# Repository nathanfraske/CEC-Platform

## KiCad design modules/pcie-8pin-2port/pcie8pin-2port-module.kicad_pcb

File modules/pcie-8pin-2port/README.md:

# PCIe 8-pin module — 2-port SKU

Standard-tier **per-cable** sensing module for the PCIe 8-pin (PCIe/GPU) power
connector. **2-port SKU: 2 cables → 4 connectors**. The 3-port variant (spec
upper bound) is a separate board in
[`../pcie-8pin-3port`](../pcie-8pin-3port). BOM target **$38** (100-qty). See spec
[§6.2](../../CEC-Platform-Ground-Truth-Spec.md).

| Item | Decision |
|---|---|
| Tier | Standard |
| SKU | **2-port** (2 cables / 4 connectors) — SKU separation from the 3-port |
| MCU | **ESP32-C6-MINI-1-N4** (v3.10; was ESP32-S3-MINI-1-N4R2). Native USB-Serial-JTAG on IO13 (D+)/IO12 (D−); ADC1 = GPIO0–6. |
| Hub link | RJ-45 8P8C shielded FTP, locking boot (J1) |
| Power path | Pass-through interposer: per cable a PSU-side **IN** + load-side **OUT** 8-pin (2×4) header; **2 cables → 4 headers**. Molex Mini-Fit Jr (PCIe/ATX 8-pin standard; 3×12V + 5×GND). Gender/footprint per the 24-pin §2.8 interposer pattern — confirm at layout. |
| Control | CAN on pair 3 (classical 500 kbps in a Standard Hub), TJA1051T/3 (U2) |
| Sensing | **Per-cable INA238** (16-bit I²C), 2 cables (U10/U11, distinct I²C addresses) — one across each cable's **0.5 mΩ** Kelvin shunt (RS1/RS2, §6.4), Vbus read on the load side. |
| Transient detection (§6.13) | **Per-cable analog DETECTION front-end** (v3.10, resolves OQ-9): INA181A2 gain-50 CSA (U20/U21) → TLV7011 hysteresis comparator (U30/U31) → board-shared firmware THRESH (MCU PWM IO14 + R10 10 kΩ / C40 100 nF) → per-cable DET → MCU GPIO, ORs into the §6.10 FREEZE trigger. Binary event (it happened + averaged envelope), not the sub-ms waveform — magnitude/shape are a PCIe Pro/Max SKU. |
| Streaming | RS-485 **not populated** (Standard); pair 2 terminated module-side |
| DETECT | 2.2 kΩ precision (R1) — CAN-only code (§2.3, OQ-6 resolved), Hub 10 kΩ/3.3 V divider; poke-and-ack tap R7 → IO10 (OQ-28) |
| Protection | No per-pin PoE/over-voltage (Standard/Pro, §2.4 v2.0); low-cap ESD diode D1 (**PESD5V0S1BA**, C5261083) on DETECT pin 8 |
| Flash/debug | USB-C (J5) on the ESP32-C6 native USB-Serial-JTAG (D+ = IO13 / D− = IO12) + BOOT/RESET buttons (SW1/SW2, TS-1088-AR02016; BOOT = IO9); VBUS ORs into +5VSB via D2 (SS34); CC1/CC2 = 5.1 kΩ |
| Decoupling | LP5907 LDO; 24-pin gold-standard tiering (2× 10 µF bulk, 1 µF LDO in/out, per-IC 100 nF) |
| BOM target | $38 (100-qty) |

## Open questions touching this board

- **OQ-9 (RESOLVED, v3.10 §6.13):** PCIe transient capture is the analog DETECTION
  ladder above — Standard sees that a transient happened (binary, into FREEZE);
  magnitude/shape are held to the PCIe Pro/Max SKUs. (OQ-57..59 gate the details.)
- **OQ-10 / OQ-12:** bundled-shunt vertical transition + high-current stackup for
  the ~40–55 A/cable shunt sites (§6.7).
- **OQ-11:** per-module shunt part selection (§6.4 table).
- *(OQ-6 module-ID encoding resolved — CAN-only modules = 2.2 kΩ.)*

## Status

Schematic generated by `scripts/gen-modules.py`; the initial PCB floorplan by
`scripts/gen-module-pcb.py` (one-shot — hand-maintained in the GUI afterwards):
4-layer, **2 oz outer / 1 oz inner** (In1 = GND, In2 = 12 V), ~110 × 66 mm, 2
cables inline top/bottom, the ESP + CAN + LDO + flash front end + RJ-45 on the
right, 4× M3 corner mounts (cables inset to clear them), CEC copper logo on the
back. **DRAFT** marker present (ERC/DRC not yet CI-gated). Next in GUI: *Update
PCB from Schematic* to pull the passives, then place/route + pour (§6.8 Kelvin
taps, §6.7 high-current transitions). Project-local library tables point at
`../../lib` via `${KIPRJMOD}`.

## Update (2026-06-06) — v3.10: ESP32-C6 MCU + §6.13 transient-detection front-end

Regenerated on the consolidated v3.10 spec:

- **MCU ESP32-S3-MINI-1-N4R2 → ESP32-C6-MINI-1-N4** (C5736265), pin map
  netlist-verified (CAN_TX/RX → pads 26/27, USB D+/D− → pads 18/17, I²C → 24/25,
  EN → 8, BOOT/IO9 → 23, DETECT_SENSE → 12, +3V3 → 3, THRESH_PWM/IO14 → 19).
  Footprint `cec-RF_Module:ESP32-C6-MINI-1`.
- **§6.13 per-cable detection front-end** (2 cables): U20/U21 **INA181A2IDBVR**
  (C2058784) + U30/U31 **TLV7011DBVR** (C702117) + board-shared R10/C40 THRESH RC
  off MCU PWM IO14. Chain netlist-verified (shunt → INA181 → comparator → THRESH →
  per-cable DET → MCU GPIO pads 28/29). **D1 PESD UL → BA** (C5261083).
- BOM regenerated (`bom/pcie8pin-2port-module-BOM-jlcpcb.csv`): **sourced 39/45**;
  open are the 0.5 mΩ shunts (OQ-11) + the Mini-Fit Jr THT power headers.
- ERC = benign only.

## PCB floorplan (2026-06-06) — condensed candidate generator (86.4 × 44 mm)

Reproduced by `scripts/gen-pcie-condensed.py` (the **parametric** PCIe analogue of the
EPS `gen-eps-condensed.py`; reuses `gen-module-pcb.py`'s emit helpers without touching the
shared generator — one script drives both PCIe SKUs by board-name arg). Built the EPS way,
with **two sub-agent passes — footprint/placement planning, then a routing game-plan**.
**86.4 × 44 mm** (4-layer, F.Cu 2 oz / In1 1 oz / In2 1 oz / B.Cu 2 oz) — condensed from the
earlier 99 × 44. Plan + diagram: `pcie2-routing-plan.png`. **All 45 schematic parts placed**
(25/25 support passives netlist-verified by `PASSIVE_SPEC` + explicitly cluster-placed — the
3 entries for the 3rd cable are correctly absent on this 2-cable SKU); DRC 0 structural apart
from a known headless false within-footprint mask-bridge artifact on a button (absent in the
GUI; the RJ-45 mouth overhangs with copper kept on-board).

- **Cable connectors = the REAL Molex 45586** (J_IN/J_OUT): **Mini-Fit Jr. right-angle,
  3rd-gen PCIe polarization, 8-circuit, Nylon UL94V-0, 2.54µm matte tin — MPN
  45586-0005** (user-confirmed keying). The footprint is the manufacturer ECAD land
  (`cec-Connector_Molex:Molex_Mini-Fit_Jr_45586_2x04_P4.20mm_Horizontal`, vendored from
  the Molex `-SD` export + its STEP): 4.20 mm pitch + **5.50 mm rows**, round ⌀2.36 mm /
  1.85 mm-drill pads, two ⌀3.0 mm snap pegs in line with the outer pins 7.3 mm forward.
  THT, consigned/hand-soldered.
- **Connectors overhang their edges** — the body+mouth hang off the top (J_IN) /
  bottom (J_OUT) edges; only the pad rows + the 2 snap pegs stay on-board. The
  footprint is native mouth-toward-+y, so J_IN is placed rot180 / J_OUT rot0 (which
  reproduces the prior pad columns, so the net map + 12 V alignment are unchanged).
  The **RJ-45 mouth overhangs the right edge** too. The 45586 snap pegs set H = 44.
- **Side-by-side sense band** per cable: 0.5 mΩ shunt vertical in the 12 V path, INA238 +
  the §6.13 INA181→TLV7011 pair beside it.
- **J1 = platform FTP jack** Kinghelm **KH-RJ45-58-8P8C** (LCSC **C2683360**,
  `cec:RJ45_FTP_Shielded_Horizontal`), SH1/SH2 → GND — matching the Hub, EPS and
  12VHPWR.
- **3 M3 mounts:** two on the logic/electronics (right) side (TR/BR corners) + **one
  centered on the connector (left) side** at (4, H/2). USB-C on the top edge.
- Dual `GND Plane` over In1 + In2 (12 V on the outers, split at the shunt), emitted
  unfilled. Routing-candidate guides on user layers (12 V pours Dwgs.User, Kelvin pairs
  Cmts.User, control→sense spine Eco1.User, CAN/USB Eco2.User). CEC logo + fab note on back.

**Next in the GUI:** *Fill All Zones*, route (§6.8 Kelvin taps, §6.7 high-current
transitions), re-DRC. Regenerate (pre-route only) with
`python3 scripts/gen-pcie-condensed.py pcie-8pin-2port` — one-shot bootstrap, refuses to
overwrite once tracks/vias exist (`--force` overrides); hand-maintained from the first route.

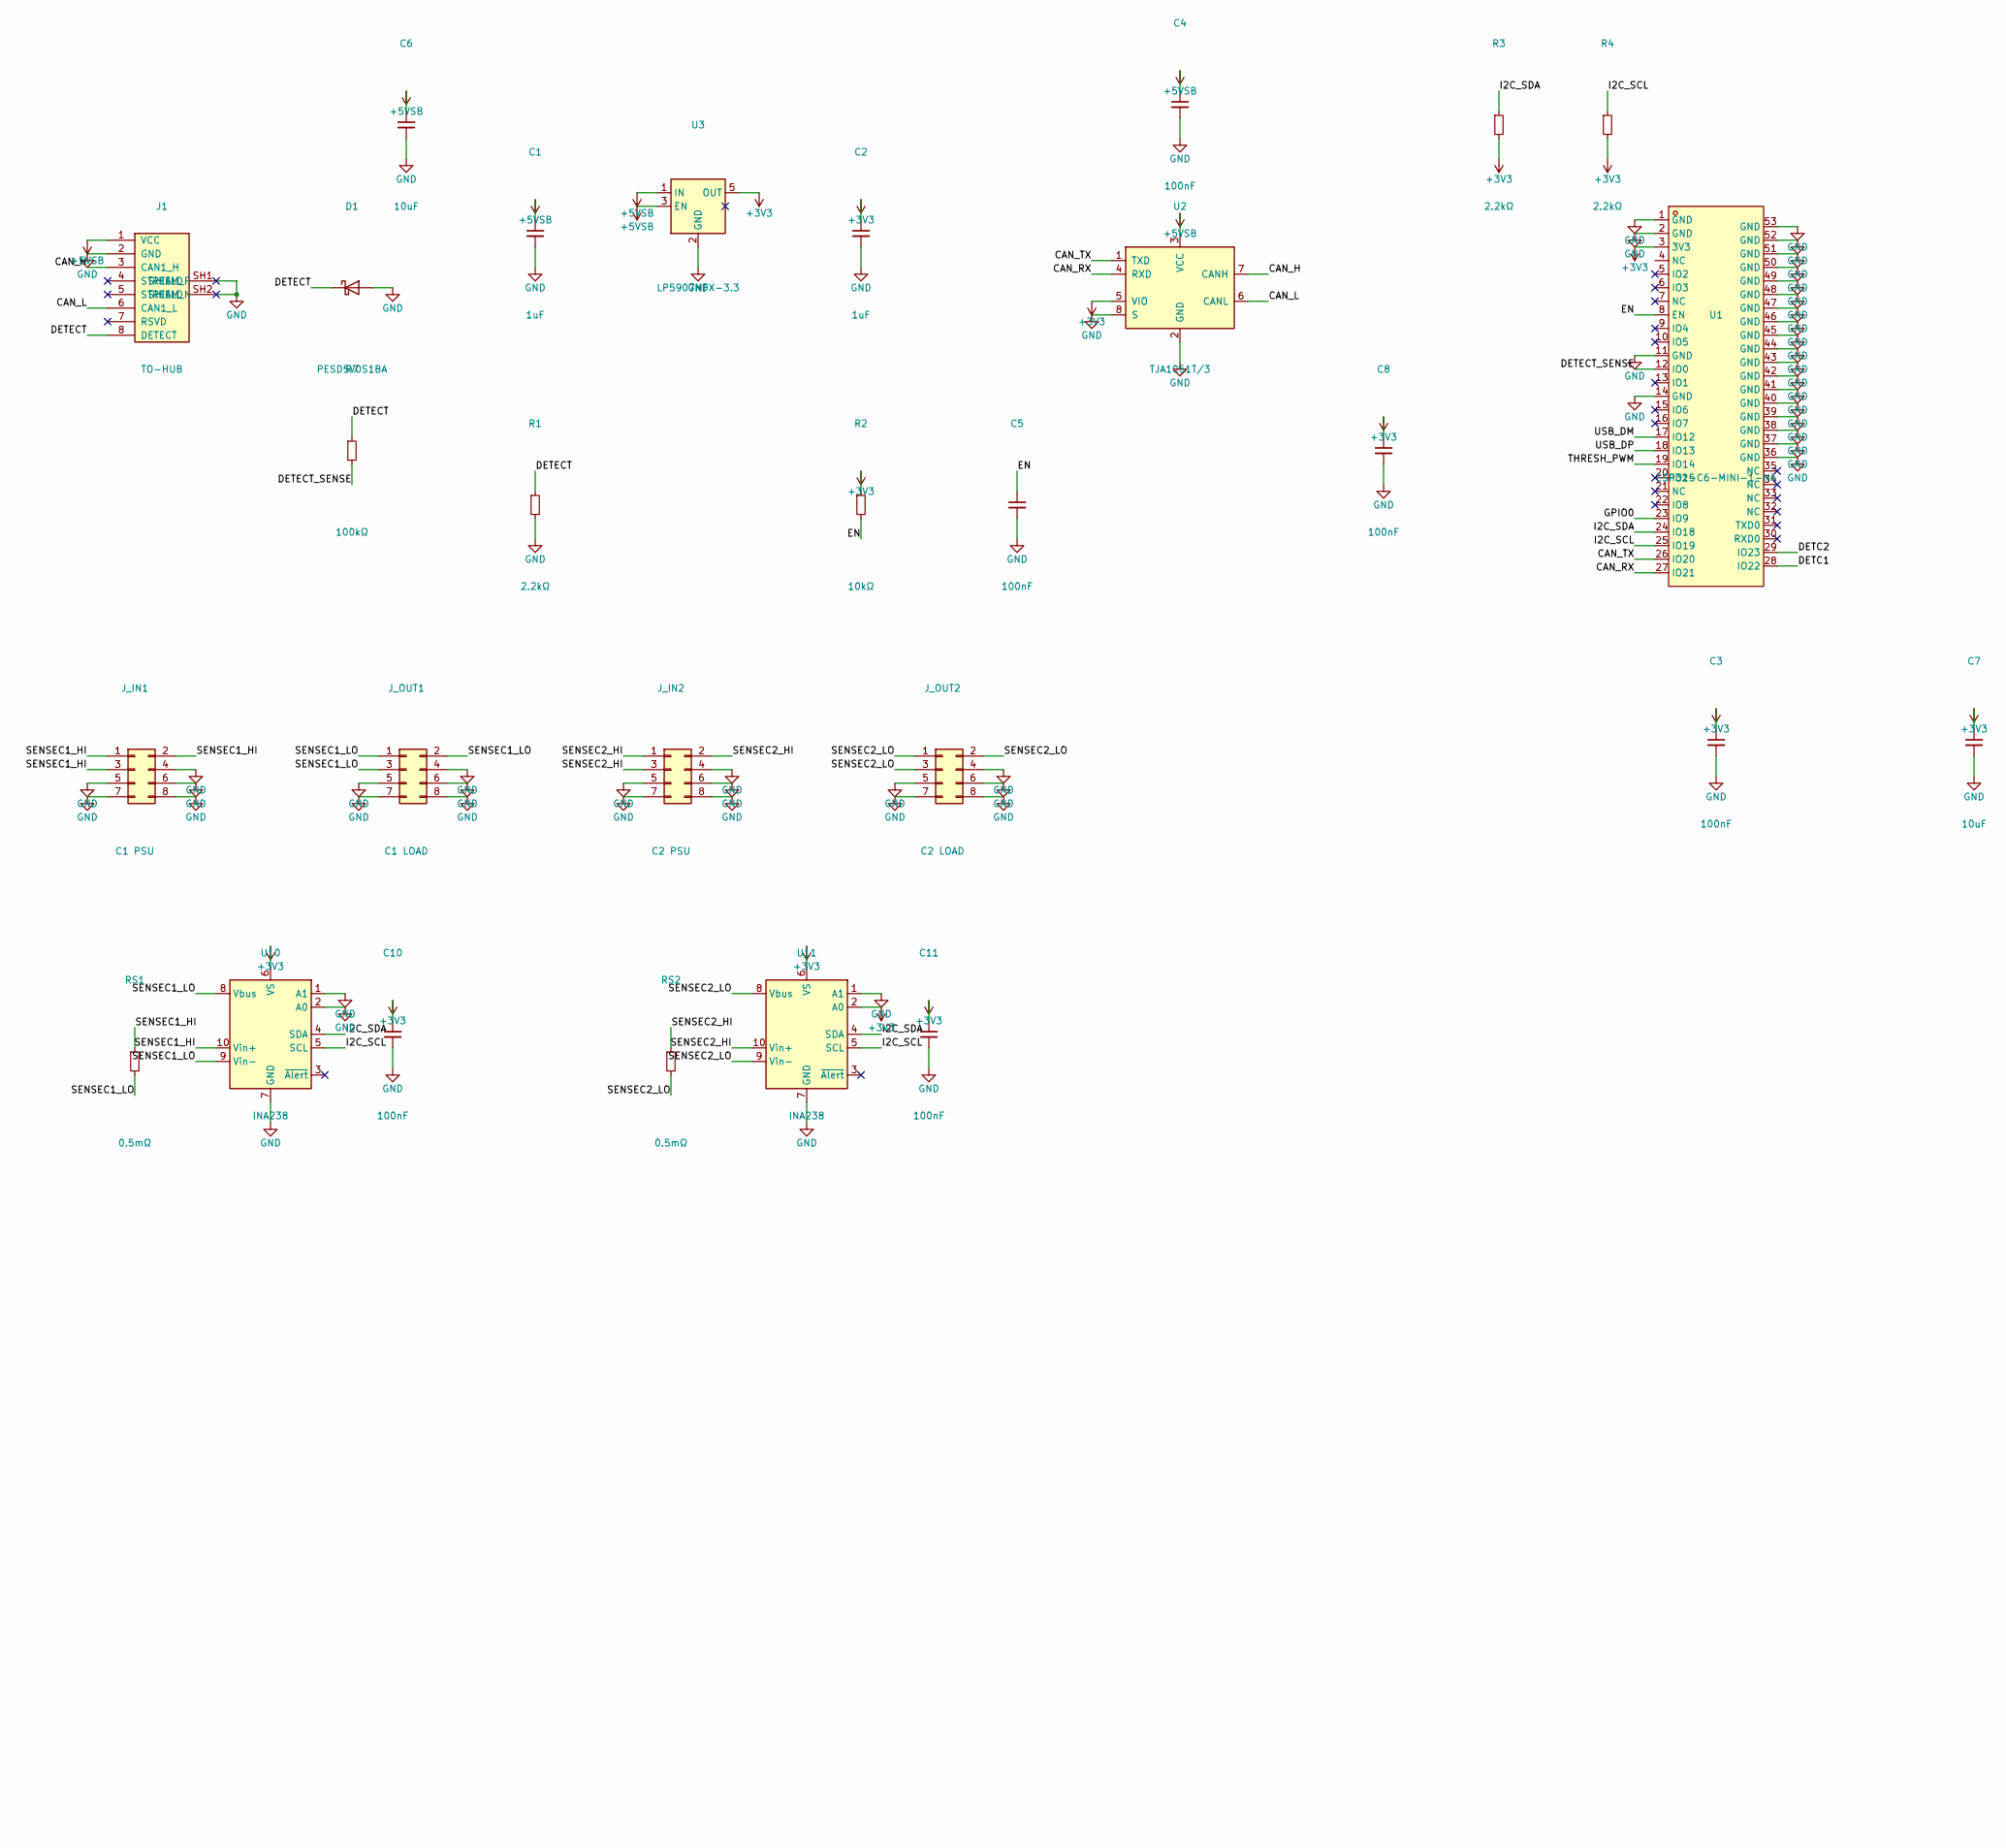
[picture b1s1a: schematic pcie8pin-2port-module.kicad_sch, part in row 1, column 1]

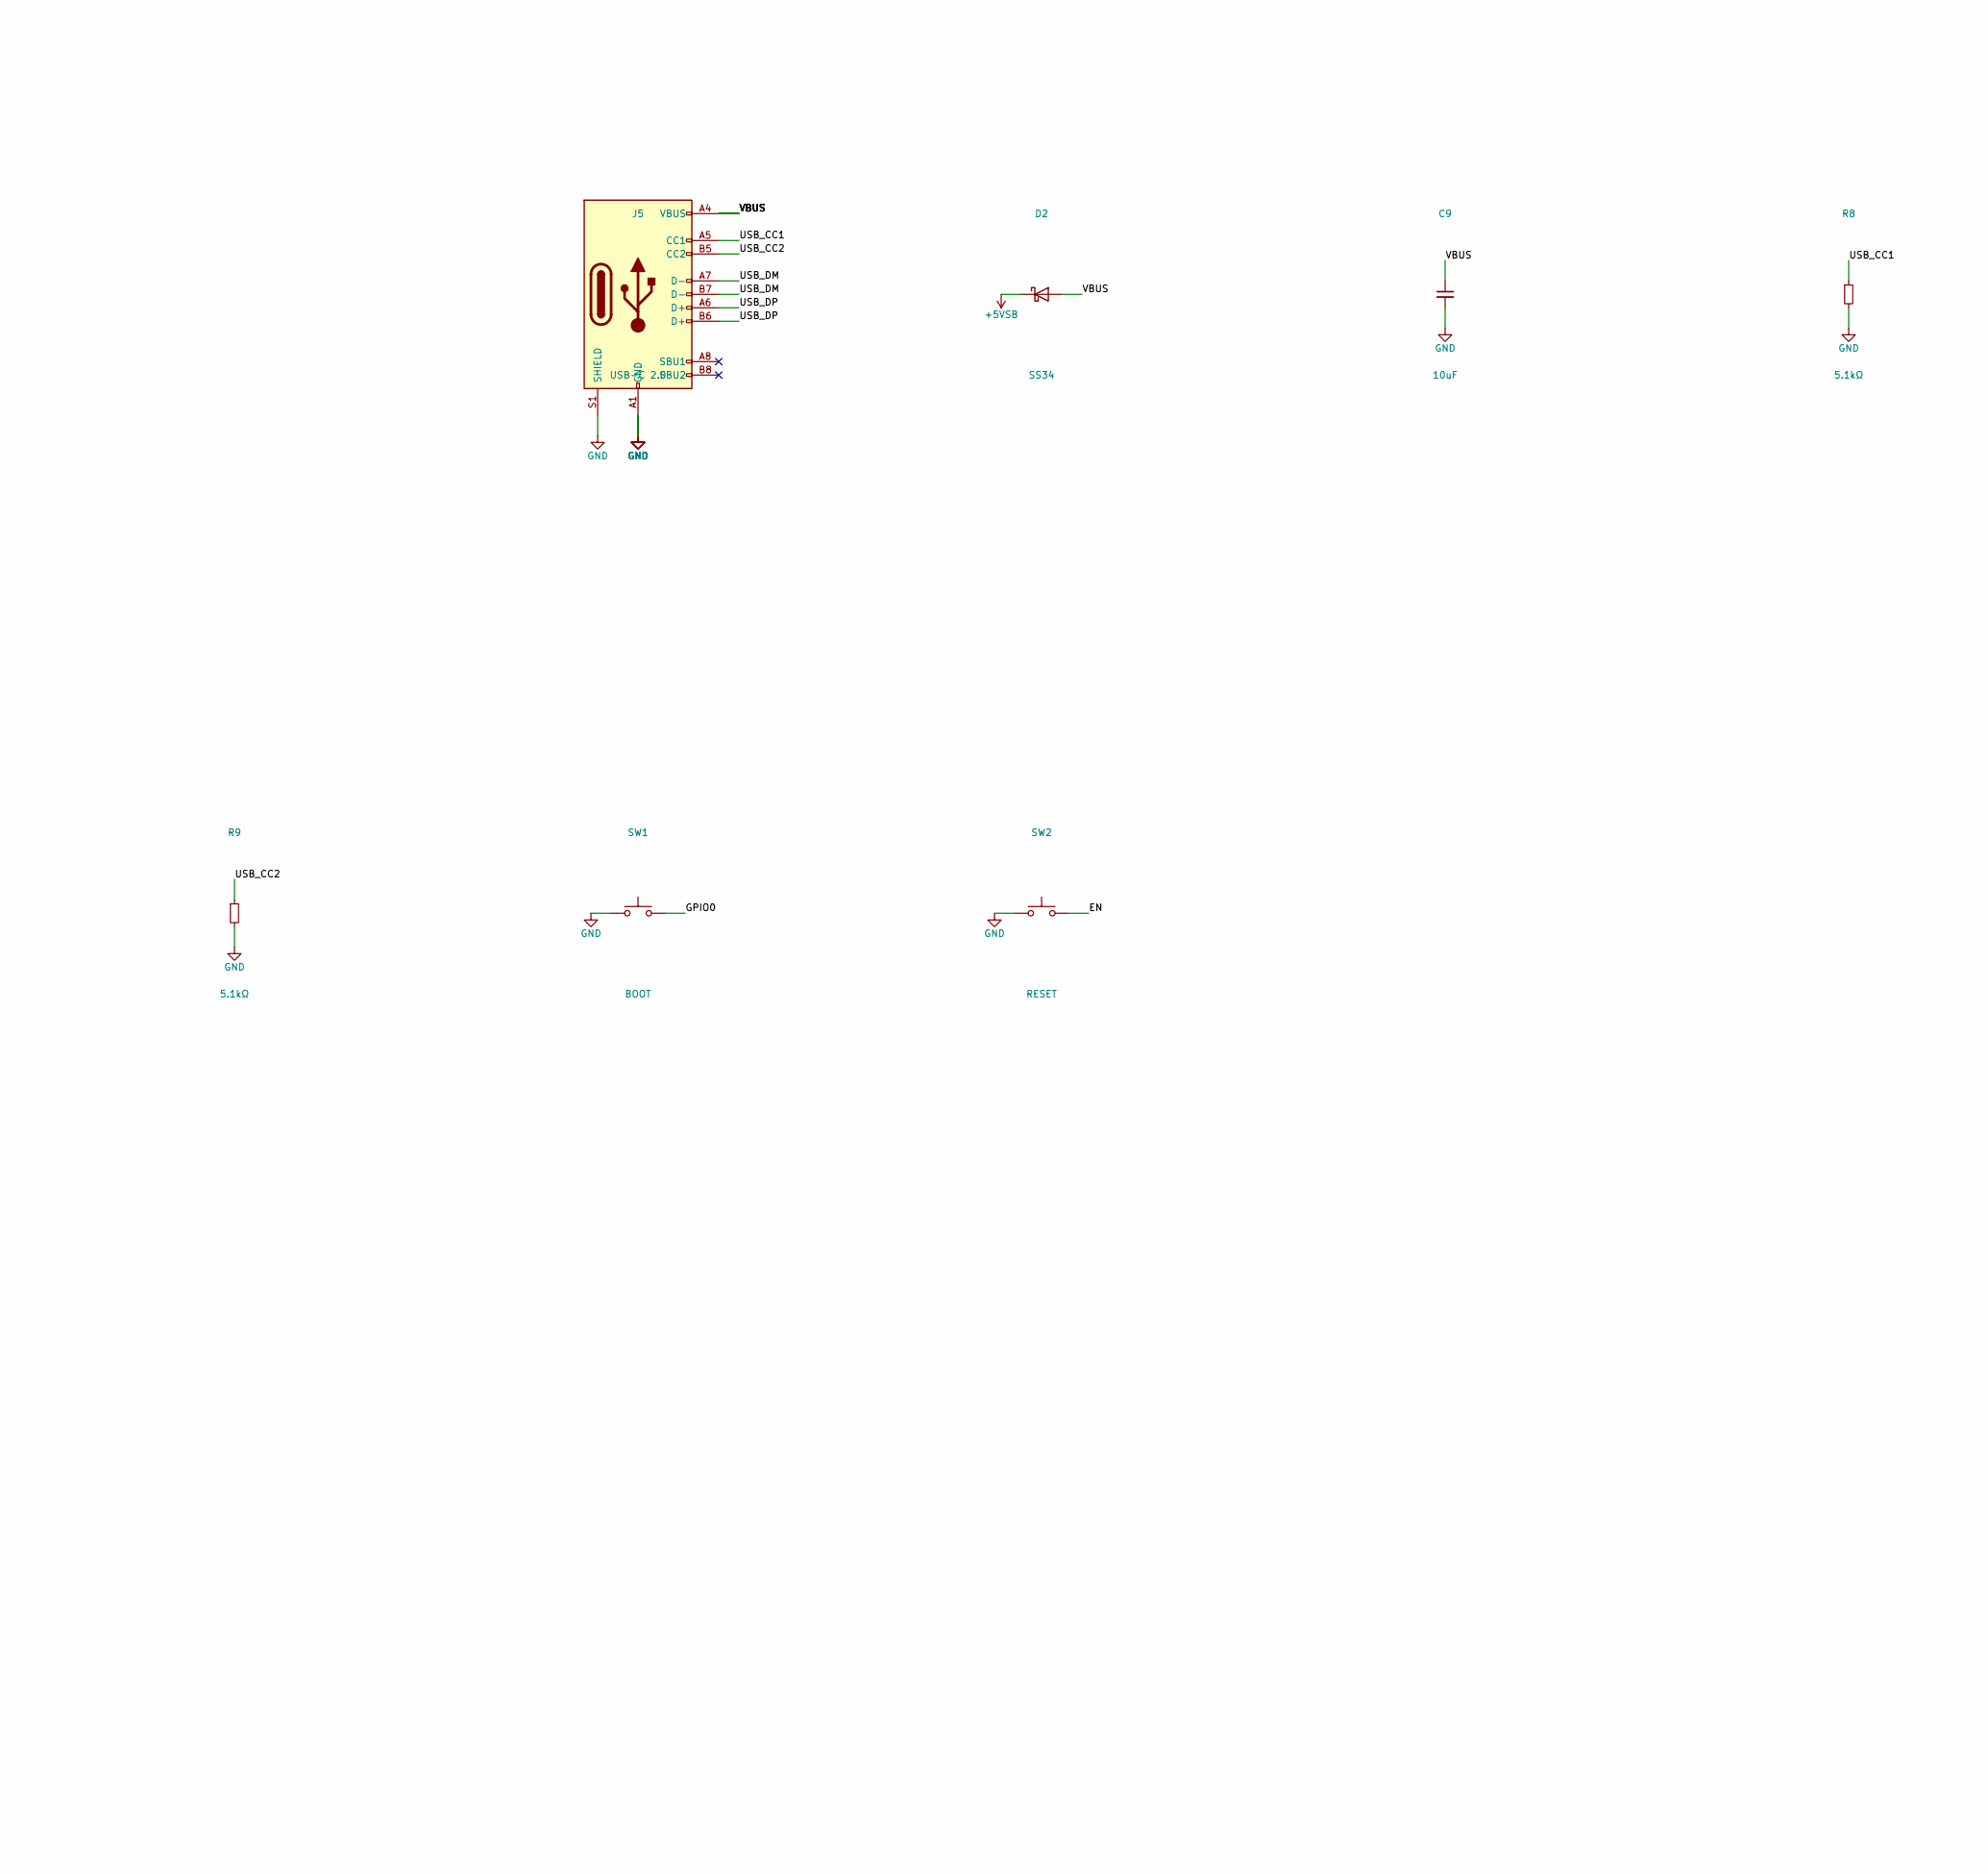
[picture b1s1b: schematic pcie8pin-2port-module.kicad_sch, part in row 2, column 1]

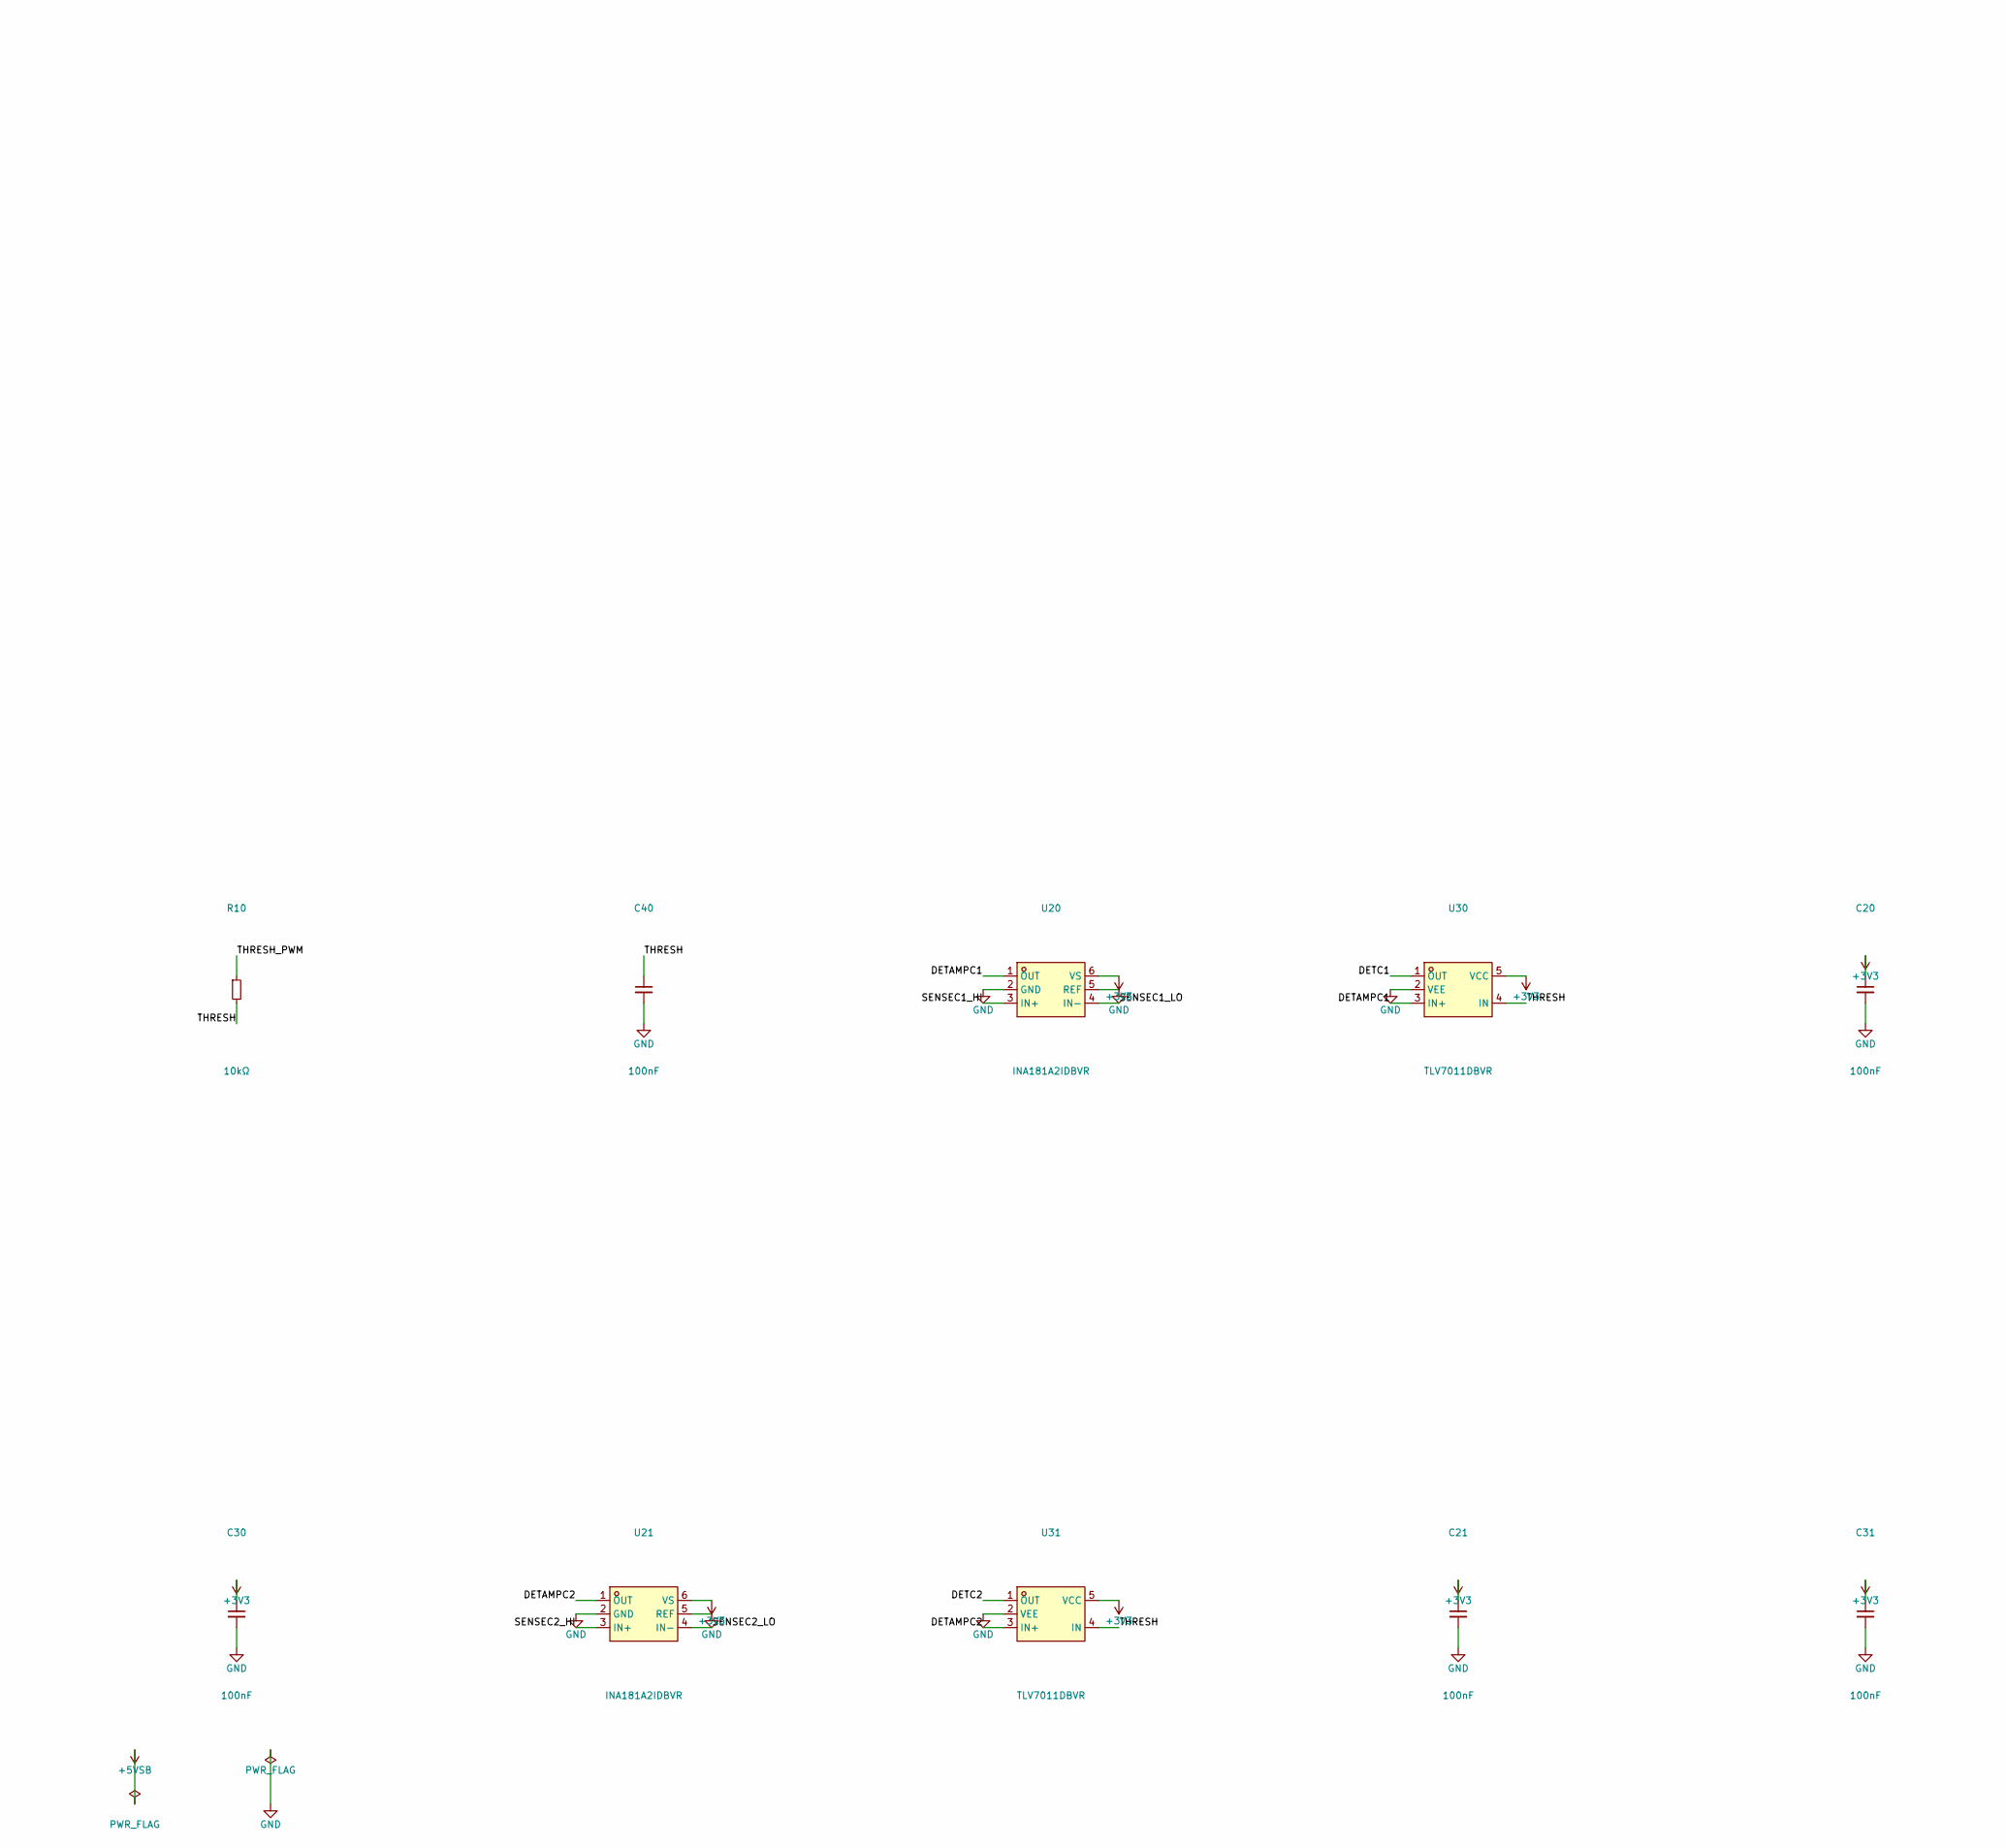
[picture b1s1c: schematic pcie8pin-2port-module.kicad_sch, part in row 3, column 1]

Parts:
C1, C2: 1uF; C_0603_1608Metric; MPN CL10B105KO8NNNC; LCSC Samsung
C3, C4, C5, C8, C10, C11, C20, C21, C30, C31, C40: 100nF; C_0402_1005Metric; MPN CL05B104KO5NNNC; LCSC Samsung
C6, C7, C9: 10uF; C_0805_2012Metric; MPN CL21A106KAYNNNE; LCSC Samsung
D1: PESD5V0S1BA; D_SOD-323; MPN PESD5V0S1BA; LCSC Nexperia
D2: SS34; D_SMA; MPN SS34; LCSC MDD
J1: TO-HUB; RJ45_FTP_Shielded_Horizontal; MPN KH-RJ45-58-8P8C; LCSC Kinghelm
J5: USB-C 2.0; USB_C_Receptacle_XKB_U262-16XN-4BVC11; MPN U262-16XN-4BVC11; LCSC XKB
J_IN1: C1 PSU; Molex_Mini-Fit_Jr_45586_2x04_P4.20mm_Horizontal; MPN 45586-0005
J_IN2: C2 PSU; Molex_Mini-Fit_Jr_45586_2x04_P4.20mm_Horizontal; MPN 45586-0005
J_OUT1: C1 LOAD; Molex_Mini-Fit_Jr_45586_2x04_P4.20mm_Horizontal; MPN 45586-0005
J_OUT2: C2 LOAD; Molex_Mini-Fit_Jr_45586_2x04_P4.20mm_Horizontal; MPN 45586-0005
R1, R3, R4: 2.2kΩ; R_0402_1005Metric; MPN 0402WGF2201TCE; LCSC UNI-ROYAL
R2, R10: 10kΩ; R_0402_1005Metric; MPN 0402WGF1002TCE; LCSC UNI-ROYAL
R7: 100kΩ; R_0402_1005Metric; MPN 0402WGF1003TCE; LCSC UNI-ROYAL
R8, R9: 5.1kΩ; R_0402_1005Metric; MPN 0402WGF5101TCE; LCSC UNI-ROYAL
RS1, RS2: 0.5mΩ; R_2512_6332Metric
SW1: BOOT; TS-1088-AR02016; MPN TS-1088-AR02016; LCSC XKB
SW2: RESET; TS-1088-AR02016; MPN TS-1088-AR02016; LCSC XKB
U1: ESP32-C6-MINI-1-N4; ESP32-C6-MINI-1; MPN ESP32-C6-MINI-1-N4; LCSC Espressif Systems
U2: TJA1051T/3; SOIC-8_3.9x4.9mm_P1.27mm; MPN TJA1051T/3; LCSC NXP
U3: LP5907MFX-3.3; SOT-23-5; MPN LP5907MFX-3.3; LCSC Texas Instruments
U10, U11: INA238; VSSOP-10_3x3mm_P0.5mm; MPN INA238AIDGSR; LCSC Texas Instruments
U20, U21: INA181A2IDBVR; SOT-23-6; MPN INA181A2IDBVR; LCSC Texas Instruments
U30, U31: TLV7011DBVR; SOT-23-5; MPN TLV7011DBVR; LCSC Texas Instruments

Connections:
+3V3: C2.1, C3.1, C7.1, C8.1, C10.1, C11.1, C20.1, C21.1, C30.1, C31.1, R2.1, R3.2, R4.2, U1.3 (3V3), U2.5 (VIO), U3.5 (OUT), U10.6 (VS), U11.2 (A0), U11.6 (VS), U20.6 (VS), U21.6 (VS), U30.5 (VCC), U31.5 (VCC)
+5VSB: C1.1, C4.1, C6.1, D2.1 (K), J1.1 (VCC), U2.3 (VCC), U3.1 (IN), U3.3 (EN)
/CAN_H: J1.3 (CAN1_H), U2.7 (CANH)
/CAN_L: J1.6 (CAN1_L), U2.6 (CANL)
/CAN_RX: U1.27 (IO21), U2.4 (RXD)
/CAN_TX: U1.26 (IO20), U2.1 (TXD)
/DETAMPC1: U20.1 (OUT), U30.3 (IN+)
/DETAMPC2: U21.1 (OUT), U31.3 (IN+)
/DETC1: U1.28 (IO22), U30.1 (OUT)
/DETC2: U1.29 (IO23), U31.1 (OUT)
/DETECT: D1.1 (K), J1.8 (DETECT), R1.1, R7.1
/DETECT_SENSE: R7.2, U1.12 (IO0)
/EN: C5.1, R2.2, SW2.2, U1.8 (EN)
/GPIO0: SW1.2, U1.23 (IO9)
/I2C_SCL: R4.1, U1.25 (IO19), U10.5 (SCL), U11.5 (SCL)
/I2C_SDA: R3.1, U1.24 (IO18), U10.4 (SDA), U11.4 (SDA)
/SENSEC1_HI: J_IN1.1, J_IN1.2, J_IN1.3, RS1.1, U10.10 (Vin+), U20.3 (IN+)
/SENSEC1_LO: J_OUT1.1, J_OUT1.2, J_OUT1.3, RS1.2, U10.8 (Vbus), U10.9 (Vin-), U20.4 (IN-)
/SENSEC2_HI: J_IN2.1, J_IN2.2, J_IN2.3, RS2.1, U11.10 (Vin+), U21.3 (IN+)
/SENSEC2_LO: J_OUT2.1, J_OUT2.2, J_OUT2.3, RS2.2, U11.8 (Vbus), U11.9 (Vin-), U21.4 (IN-)
/THRESH: C40.1, R10.2, U30.4 (IN), U31.4 (IN)
/THRESH_PWM: R10.1, U1.19 (IO14)
/USB_CC1: J5.A5 (CC1), R8.1
/USB_CC2: J5.B5 (CC2), R9.1
/USB_DM: J5.A7 (D-), J5.B7 (D-), U1.17 (IO12)
/USB_DP: J5.A6 (D+), J5.B6 (D+), U1.18 (IO13)
/VBUS: C9.1, D2.2 (A), J5.A4 (VBUS), J5.A9 (VBUS), J5.B4 (VBUS), J5.B9 (VBUS)
GND: C1.2, C2.2, C3.2, C4.2, C5.2, C6.2, C7.2, C8.2, C9.2, C10.2, C11.2, C20.2, C21.2, C30.2, C31.2, C40.2, D1.2 (A), J1.2 (GND), J1.SH1 (SHIELD), J1.SH2 (SHIELD), J5.A1 (GND), J5.A12 (GND), J5.B1 (GND), J5.B12 (GND), J5.S1 (SHIELD), J_IN1.4, J_IN1.5, J_IN1.6, J_IN1.7, J_IN1.8, J_IN2.4, J_IN2.5, J_IN2.6, J_IN2.7, J_IN2.8, J_OUT1.4, J_OUT1.5, J_OUT1.6, J_OUT1.7, J_OUT1.8, J_OUT2.4, J_OUT2.5, J_OUT2.6, J_OUT2.7, J_OUT2.8, R1.2, R8.2, R9.2, SW1.1, SW2.1, U1.1 (GND), U1.2 (GND), U1.11 (GND), U1.14 (GND), U1.36 (GND), U1.37 (GND), U1.38 (GND), U1.39 (GND), U1.40 (GND), U1.41 (GND), U1.42 (GND), U1.43 (GND), U1.44 (GND), U1.45 (GND), U1.46 (GND), U1.47 (GND), U1.48 (GND), U1.49 (GND), U1.50 (GND), U1.51 (GND), U1.52 (GND), U1.53 (GND), U2.2 (GND), U2.8 (S), U3.2 (GND), U10.1 (A1), U10.2 (A0), U10.7 (GND), U11.1 (A1), U11.7 (GND), U20.2 (GND), U20.5 (REF), U21.2 (GND), U21.5 (REF), U30.2 (VEE), U31.2 (VEE); also elsewhere on the board

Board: 4 copper layers, 49 parts (1 on the bottom side), 28 nets, no tracks yet.

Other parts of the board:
H1, H2, H3: MountingHole_3.2mm_M3_Pad_Via
LOGO1: CEC_Logo_Copper

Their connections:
GND: H1.1, H2.1, H3.1; also elsewhere on the board

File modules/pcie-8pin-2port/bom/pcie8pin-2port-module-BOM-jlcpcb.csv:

Comment,Designator,Footprint,LCSC Part #
1uF,"C1,C2",C_0603_1608Metric,C15849
100nF,"C3,C4,C5,C8,C10,C11,C20,C21,C30,C31,C40",C_0402_1005Metric,C1525
10uF,"C6,C7,C9",C_0805_2012Metric,C15850
PESD5V0S1BA,D1,D_SOD-323,C5261083
SS34,D2,D_SMA,C8678
TO-HUB,J1,RJ45_FTP_Shielded_Horizontal,C2683360
USB-C 2.0,J5,USB_C_Receptacle_XKB_U262-16XN-4BVC11,C2765186
C1 PSU,J_IN1,Molex_Mini-Fit_Jr_45586_2x04_P4.20mm_Horizontal,
C2 PSU,J_IN2,Molex_Mini-Fit_Jr_45586_2x04_P4.20mm_Horizontal,
C1 LOAD,J_OUT1,Molex_Mini-Fit_Jr_45586_2x04_P4.20mm_Horizontal,
C2 LOAD,J_OUT2,Molex_Mini-Fit_Jr_45586_2x04_P4.20mm_Horizontal,
2.2kΩ,"R1,R3,R4",R_0402_1005Metric,C25879
10kΩ,"R2,R10",R_0402_1005Metric,C25744
100kΩ,R7,R_0402_1005Metric,C25741
5.1kΩ,"R8,R9",R_0402_1005Metric,C25905
0.5mΩ,"RS1,RS2",R_2512_6332Metric,
BOOT,SW1,TS-1088-AR02016,C720477
RESET,SW2,TS-1088-AR02016,C720477
ESP32-C6-MINI-1-N4,U1,ESP32-C6-MINI-1,C5736265
TJA1051T/3,U2,SOIC-8_3.9x4.9mm_P1.27mm,C38695
LP5907MFX-3.3,U3,SOT-23-5,C80670
INA238,"U10,U11",VSSOP-10_3x3mm_P0.5mm,C2868250
INA181A2IDBVR,"U20,U21",SOT-23-6,C2058784
TLV7011DBVR,"U30,U31",SOT-23-5,C702117

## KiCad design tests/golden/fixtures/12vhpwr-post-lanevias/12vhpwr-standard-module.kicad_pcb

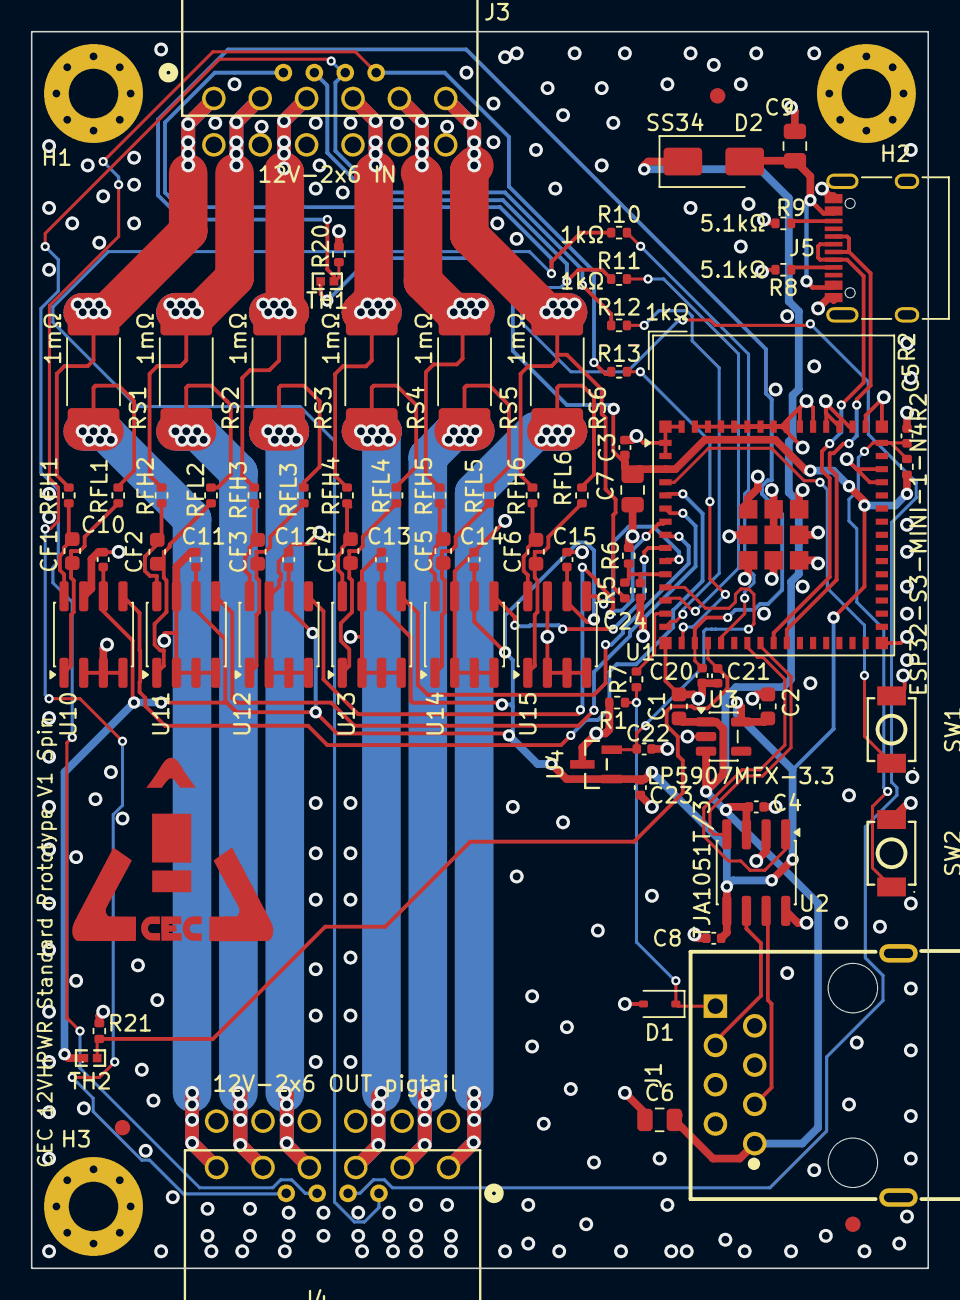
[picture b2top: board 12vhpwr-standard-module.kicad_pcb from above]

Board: 4 copper layers, 58.0 x 80.0 mm, 84 parts (0 on the bottom side), 58 nets.

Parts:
C1, C2: 1uF; C_0603_1608Metric
C3, C4, C5, C8, C10, C11, C12, C13, C14, C15, C20, C21, C22, C23: 100nF; C_0402_1005Metric
C6, C7, C9: 10uF; C_0805_2012Metric
C24: 1nF; C_0402_1005Metric
CF1, CF2, CF3, CF4, CF5, CF6: 470nF; C_0603_1608Metric
D1: PESD5V0S1BA; D_SOD-323
D2: SS34; D_SMA
FID1, FID2, FID3: Fiducial_1mm_Mask2mm
H1, H2, H3: MountingHole_3.2mm_M3_Pad_Via
J1: TO-HUB; RJ45_FTP_Shielded_Horizontal
J3: 12V-2x6 IN; CEC_12V2x6_Horizontal
J4: 12V-2x6 OUT pigtail; CEC_12V2x6_Horizontal
J5: USB-C 2.0; USB_C_Receptacle_XKB_U262-16XN-4BVC11
LOGO1: CEC_Logo_Copper
R1: 2.2kΩ; R_0402_1005Metric
R2, R6, R20, R21: 10kΩ; R_0402_1005Metric
R5: 47kΩ; R_0402_1005Metric
R7: 100kΩ; R_0402_1005Metric
R8, R9: 5.1kΩ; R_0402_1005Metric
R10, R11, R12, R13: 1kΩ; R_0402_1005Metric
RFH1, RFH2, RFH3, RFH4, RFH5, RFH6: 10Ω; R_0402_1005Metric
RFL1, RFL2, RFL3, RFL4, RFL5, RFL6: 10Ω; R_0402_1005Metric
RS1, RS2, RS3, RS4, RS5, RS6: 1mΩ; R_2512_6332Metric
SW1: BOOT; TS-1088-AR02016
SW2: RESET; TS-1088-AR02016
TH1, TH2: NTC 10k; NTC_0402_1005Metric
U1: ESP32-S3-MINI-1-N4R2; ESP32-S2-MINI-1_NoAntKeepout
U2: TJA1051T/3; SOIC-8_3.9x4.9mm_P1.27mm
U3: LP5907MFX-3.3; SOT-23-5
U4: REF3030; REF3030_DBZ3
U10, U11, U12, U13, U14, U15: INA240A3; SOIC-8_3.9x4.9mm_P1.27mm

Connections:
+3V3: C2.1, C3.1, C7.1, C8.1, C10.1, C11.1, C12.1, C13.1, C14.1, C15.1, C23.1, R2.1, TH1.1, TH2.1, U1.3 (3V3), U2.5 (VIO), U3.5 (OUT), U4.1 (IN), U10.6 (V+), U11.6 (V+), U12.6 (V+), U13.6 (V+), U14.6 (V+), U15.6 (V+)
+5VSB: C1.1, C4.1, C6.1, D2.1 (K), J1.1 (VCC), U2.3 (VCC), U3.1 (IN), U3.3 (EN)
/CAN_H: J1.3 (CAN1_H), U2.7 (CANH)
/CAN_L: J1.6 (CAN1_L), U2.6 (CANL)
/CAN_RX: U1.22 (IO18), U2.4 (RXD)
/CAN_TX: U1.21 (IO17), U2.1 (TXD)
/DETECT: D1.1 (K), J1.8 (DETECT), R1.1, R7.1
/DETECT_SENSE: R7.2, U1.14 (IO10)
/EN: C5.1, R2.2, SW2.2, U1.45 (EN)
/GPIO0: SW1.2, U1.4 (IO0)
/IN1_N: CF1.2, RFL1.2, U10.1 (-)
/IN1_P: CF1.1, RFH1.2, U10.8 (+)
/IN2_N: CF2.2, RFL2.2, U11.1 (-)
/IN2_P: CF2.1, RFH2.2, U11.8 (+)
/IN3_N: CF3.2, RFL3.2, U12.1 (-)
/IN3_P: CF3.1, RFH3.2, U12.8 (+)
/IN4_N: CF4.2, RFL4.2, U13.1 (-)
/IN4_P: CF4.1, RFH4.2, U13.8 (+)
/IN5_N: CF5.2, RFL5.2, U14.1 (-)
/IN5_P: CF5.1, RFH5.2, U14.8 (+)
/IN6_N: CF6.2, RFL6.2, U15.1 (-)
/IN6_P: CF6.1, RFH6.2, U15.8 (+)
/ISENSEP1: U1.5 (IO1), U10.5
/ISENSEP2: U1.6 (IO2), U11.5
/ISENSEP3: U1.7 (IO3), U12.5
/ISENSEP4: U1.8 (IO4), U13.5
/ISENSEP5: U1.9 (IO5), U14.5
/ISENSEP6: U1.10 (IO6), U15.5
/SB_CBL_PRES: J3.16 (SENSE), J4.16 (SENSE), R13.1
/SB_CBL_PRES_GPIO: R13.2, U1.16 (IO12)
/SB_PWR_STABLE: J3.15 (SENSE), J4.15 (SENSE), R12.1
/SB_PWR_STABLE_GPIO: R12.2, U1.15 (IO11)
/SB_SENSE0: J3.13 (SENSE), J4.13 (SENSE), R10.1
/SB_SENSE0_GPIO: R10.2, U1.19 (IO15)
/SB_SENSE1: J3.14 (SENSE), J4.14 (SENSE), R11.1
/SB_SENSE1_GPIO: R11.2, U1.13 (IO9)
/SENSEP1_HI: J3.1 (+12V), RFH1.1, RS1.1
/SENSEP1_LO: J4.6 (+12V), RFL1.1, RS1.2
/SENSEP2_HI: J3.2 (+12V), RFH2.1, RS2.1
/SENSEP2_LO: J4.5 (+12V), RFL2.1, RS2.2
/SENSEP3_HI: J3.3 (+12V), RFH3.1, RS3.1
/SENSEP3_LO: J4.4 (+12V), RFL3.1, RS3.2
/SENSEP4_HI: J3.4 (+12V), RFH4.1, RS4.1
/SENSEP4_LO: J4.3 (+12V), RFL4.1, RS4.2
/SENSEP5_HI: J3.5 (+12V), RFH5.1, RS5.1
/SENSEP5_LO: J4.2 (+12V), RFL5.1, RS5.2
/SENSEP6_HI: J3.6 (+12V), R5.1, RFH6.1, RS6.1
/SENSEP6_LO: J4.1 (+12V), RFL6.1, RS6.2
/TEMP1: C20.1, R20.1, TH1.2, U1.17 (IO13)
/TEMP2: C21.1, R21.1, TH2.2, U1.18 (IO14)
/USB_CC1: J5.A5 (CC1), R8.1
/USB_CC2: J5.B5 (CC2), R9.1
/USB_DM: J5.A7 (D-), J5.B7 (D-), U1.23 (USB_D-)
/USB_DP: J5.A6 (D+), J5.B6 (D+), U1.24 (USB_D+)
/VBUS: C9.1, D2.2 (A), J5.A4 (VBUS), J5.A9 (VBUS), J5.B4 (VBUS), J5.B9 (VBUS)
/VRAIL_DIV: C24.1, R5.2, R6.1, U1.11 (IO7)
/VREF: C22.1, U1.12 (IO8), U4.2 (OUT)
GND: C1.2, C2.2, C3.2, C4.2, C5.2, C6.2, C7.2, C8.2, C9.2, C10.2, C11.2, C12.2, C13.2, C14.2, C15.2, C20.2, C21.2, C22.2, C23.2, C24.2, D1.2 (A), H1.1, H2.1, H3.1, J1.2 (GND), J1.SH1 (SHIELD), J1.SH2 (SHIELD), J3.7 (GND), J3.8 (GND), J3.9 (GND), J3.10 (GND), J3.11 (GND), J3.12 (GND), J4.7 (GND), J4.8 (GND), J4.9 (GND), J4.10 (GND), J4.11 (GND), J4.12 (GND), J5.A1 (GND), J5.A12 (GND), J5.B1 (GND), J5.B12 (GND), J5.S1 (SHIELD), R1.2, R6.2, R8.2, R9.2, R20.2, R21.2, SW1.1, SW2.1, U1.1 (GND), U1.2 (GND), U1.42 (GND), U1.43 (GND), U1.46 (GND), U1.47 (GND), U1.48 (GND), U1.49 (GND), U1.50 (GND), U1.51 (GND), U1.52 (GND), U1.53 (GND), U1.54 (GND), U1.55 (GND), U1.56 (GND), U1.57 (GND), U1.58 (GND), U1.59 (GND), U1.60 (GND), U1.61 (GND), U1.62 (GND), U1.63 (GND), U1.64 (GND), U1.65 (GND), U2.2 (GND), U2.8 (S), U3.2 (GND), U4.3 (GND), U10.2 (GND), U10.3 (REF2), U10.4 (GND), U10.7 (REF1), U11.2 (GND), U11.3 (REF2), U11.4 (GND), U11.7 (REF1), U12.2 (GND), U12.3 (REF2), U12.4 (GND), U12.7 (REF1), U13.2 (GND), U13.3 (REF2), U13.4 (GND), U13.7 (REF1), U14.2 (GND), U14.3 (REF2), U14.4 (GND), U14.7 (REF1), U15.2 (GND), U15.3 (REF2), U15.4 (GND), U15.7 (REF1)
